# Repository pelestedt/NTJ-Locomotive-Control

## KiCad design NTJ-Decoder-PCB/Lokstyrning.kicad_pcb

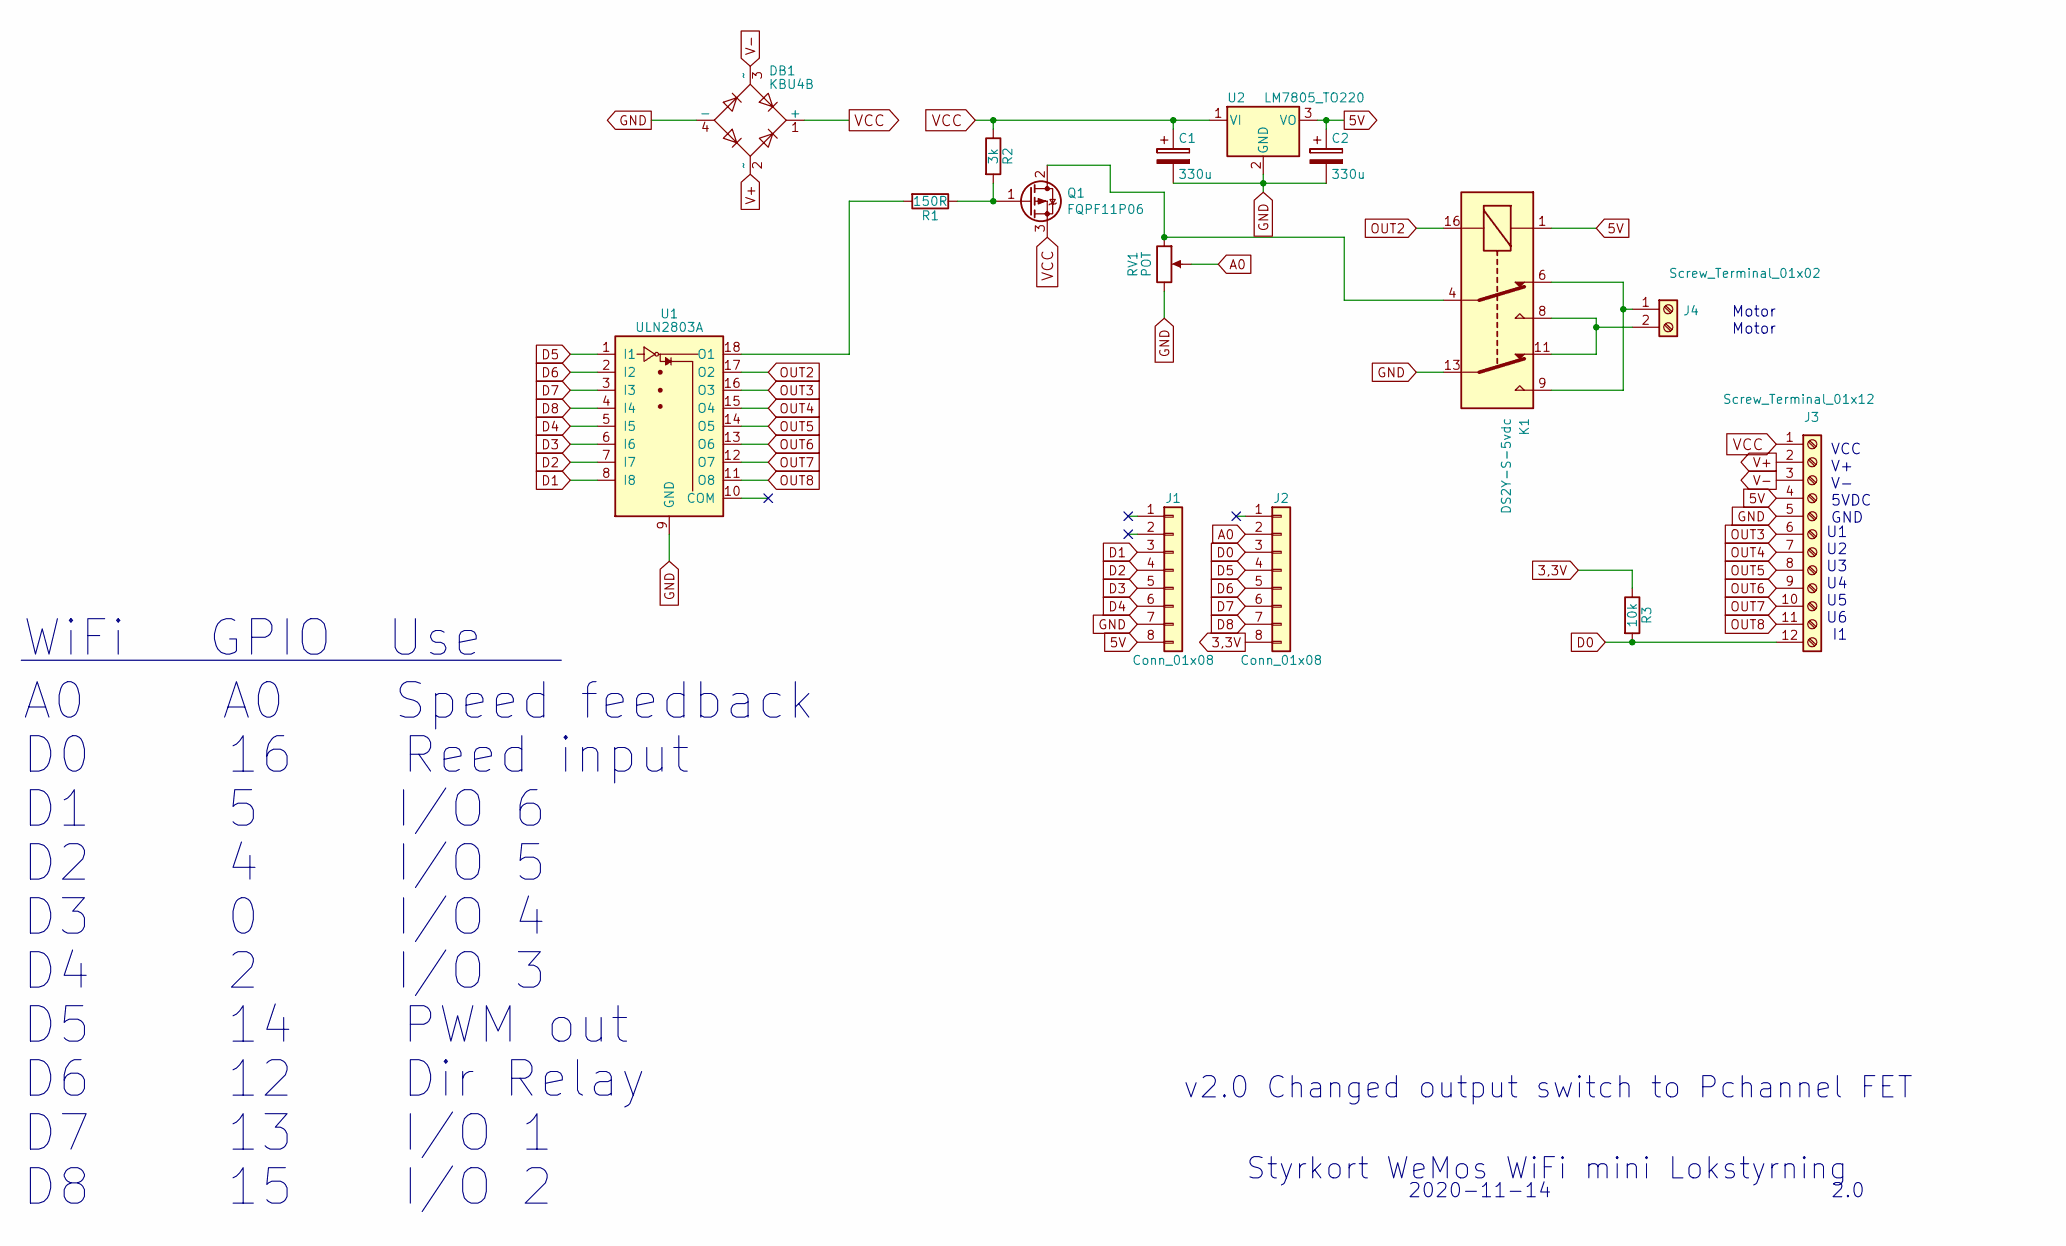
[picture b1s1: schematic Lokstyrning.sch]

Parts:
C1, C2: 330u; CP_Radial_D8.0mm_P5.00mm
DB1: KBU4B; Diode_Bridge_Vishay_KBU
J1, J2: Conn_01x08; Molex_SPOX-5267_22-03-5085_08x2.54mm_Straight
J3: Screw_Terminal_01x12; WAGO_734_12Pin_Straight_RuggedPads
J4: Screw_Terminal_01x02; WAGO_734_2pin_Straight_RuggedPads
K1: DS2Y-S-5vdc; Relay_SPST_OMRON-G5Q
Q1: FQPF11P06; TO-220_Vertical
R1: 150R; R_Axial_DIN0207_L6.3mm_D2.5mm_P10.16mm_Horizontal
R2: 3k; R_Axial_DIN0207_L6.3mm_D2.5mm_P10.16mm_Horizontal
R3: 10k; R_Axial_DIN0207_L6.3mm_D2.5mm_P10.16mm_Horizontal
RV1: POT; Potentiometer_Trimmer_ACP_CA14h5_Vertical_Px5.0mm_Py10.0mm
U1: ULN2803A; DIP-18_W7.62mm_LongPads
U2: LM7805_TO220; TO-220_Vertical

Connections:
3,3V: J2.8, R3.1
5V: C2.1, J1.8, J3.4, K1.1, U2.3 (VO)
A0: J2.2, RV1.2
D0: J2.3, J3.12, R3.2
D1: J1.3, U1.8 (I8)
D2: J1.4, U1.7 (I7)
D3: J1.5, U1.6 (I6)
D4: J1.6, U1.5 (I5)
D5: J2.4, U1.1 (I1)
D6: J2.5, U1.2 (I2)
D7: J2.6, U1.3 (I3)
D8: J2.7, U1.4 (I4)
GND: C1.2, C2.2, DB1.4 (-), J1.7, J3.5, K1.13, RV1.3, U1.9 (GND), U2.2 (GND)
unnamed: J4.1, K1.6, K1.9
unnamed: J4.2, K1.8, K1.11
unnamed: K1.4, Q1.2 (D), RV1.1
unnamed: Q1.1 (G), R1.1, R2.2
unnamed: R1.2, U1.18 (O1)
OUT2: K1.16, U1.17 (O2)
OUT3: J3.6, U1.16 (O3)
OUT4: J3.7, U1.15 (O4)
OUT5: J3.8, U1.14 (O5)
OUT6: J3.9, U1.13 (O6)
OUT7: J3.10, U1.12 (O7)
OUT8: J3.11, U1.11 (O8)
V+: DB1.2 (~~), J3.2
V-: DB1.3 (~~), J3.3
VCC: C1.1, DB1.1 (+), J3.1, Q1.3 (S), R2.1, U2.1 (VI)

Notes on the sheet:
D0 16 Reed input
D1 5 I/O 6
D2 4 I/O 5
A0 A0 Speed feedback
WiFi GPIO Use
D3 0 I/O 4
D4 2 I/O 3
D5 14 PWM out
D6 12 Dir Relay
D7 13 I/O 1
D8 15 I/O 2
Styrkort WeMos WiFi mini Lokstyrning
2020-11-14
2.0
U1 U2 U3 U4 U5 U6 I1
VCC V+ V- 5VDC GND
Motor Motor
v2.0 Changed output switch to Pchannel FET

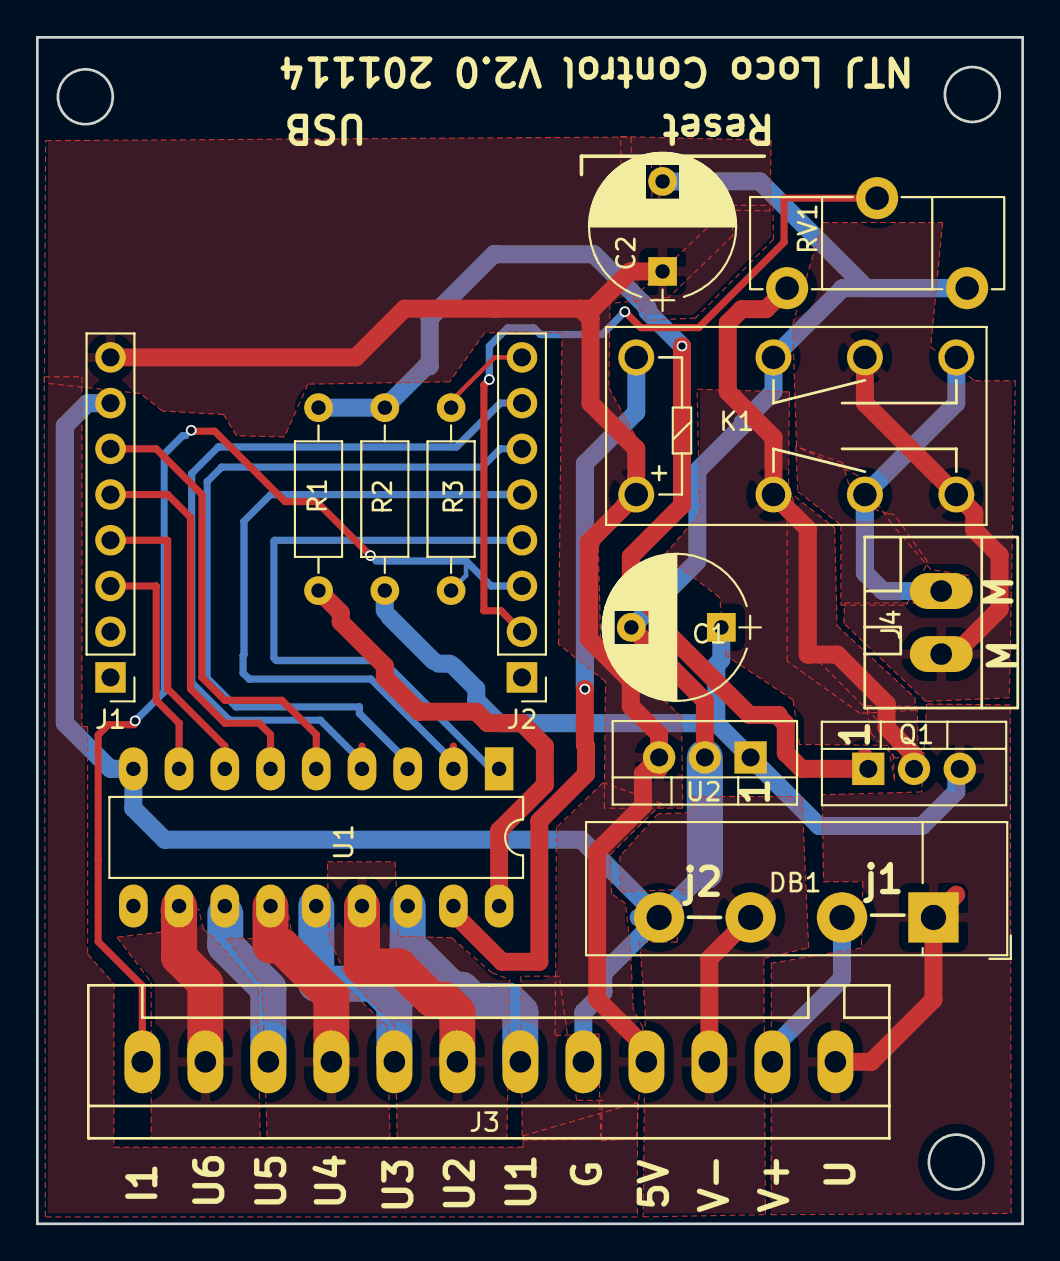
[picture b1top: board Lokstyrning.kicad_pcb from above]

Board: 2 copper layers, 54.7 x 65.9 mm, 15 parts (0 on the bottom side), 28 nets.

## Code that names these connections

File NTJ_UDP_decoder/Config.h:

/*
   Config.h

*/

/* Maximum WiFi clients that can be connected to WiThrottle */

String Configstring = "";         // a String to hold incoming data
boolean configmode = false;
int Inaddr;
String Configuration;
String Data;


//Main loop declarations
unsigned long last25run = 0;
unsigned long last50run = 0;
unsigned long last100run = 0;
unsigned long last400run = 0;
unsigned long last1000run = 0;
/* Define Control board I/O signals */
#define OUT1  D7 /*Define which GPIO corresponds to which output on the board*/
#define OUT2  D8
#define OUT3  D4
#define OUT4  D3
#define OUT5  D2
#define OUT6  D1
#define PWM  D5 /* Defines the GPIO for the PWM transistor control*/
#define DIR  D6 /* Defines the GPIO for the direction relay control*/
#define IN  D0 /* Defines the GPIO for the LED on the control board*/


long throttle_speed = 0; //0 to 126
int set_direction = 1; //1=forwrd 0=reverse
String namn;

long last=0;
long lastprint=0;

//getUDPdata declarations

String STASSID = "NTJ";
String STAPSK =  "NTJNTJ01";
int packetSize=0;

int myID = 999;
String Seq;

unsigned int localPort = 8888;      // local port to listen on
long lastparam1 = 0;
byte FunctionKey[30];

// buffer for sending data
char packetBuffer[20 + 1]; //buffer to hold incoming packet,

WiFiUDP Udp;

//Variabler lagrade i EEprom med defaultvärden angivna här
byte acceleration_time = 10; // FSet the time in seconds it should take for the locomotive to accelerate from standstill to full speed
byte deceleration_time = 10; //Set the time in seconds it should take for the locomotive to stop from full speed
int pwmfrq = 300;
int zero_speed = 10; //Set the PWM value where the locomotive, without load,starts to move
int fullspeed = 100;
int slowspeed = 75;
int halfspeed = 50;
int Shuntingspeed = 30;
int max_pulserate = 50;    //time between pulses in ms. If set to 0 the output will be only ON/OFF
int min_pulserate = 1000; //time between pulses in ms.If set to 0 the output will be only ON/OFF
int pulselength = 3;      //length of the sound generating puls relative the time between pulses in (1/(pulselength*actual pulselength))
int startwhistle = 20;
int approachwhistle = 30;
int smoke_timer = 0;
int creepspeed = 10;
int mindwell = 60;
int maxdwell = 240;
String ssid = "Ny_dekoder";
String loco_name = "Nytt_lok";
String password = "12345678";
int port = 44;
String hostn = "Ny_thserver";


//25ms declarations
boolean EMS = false;
boolean EMS_stopped = false;
float set_speed = 0;
float desired_speed = 0;
float current_PWM = 0;
float read_speed = 0;
float reglerfaktor = 40;
//int fixedpwm=50;

//50ms declarations
byte NSphase = 0;
byte NSRphase = 0;

//100ms declarations
byte NWphase = 0;
long nextwhistle = 0;


//400ms declarations
boolean NEXTSTATION = false;
boolean NEXTSTATIONREMOTE = false;
boolean PENDULUM = false;
boolean NEXTTIMER = false;
boolean sound = false;
boolean smoke = false;
boolean shunting = false;

//1000ms declarations
int smokeon = 0;

//Pendulum declarations
byte Pphase = 0;
long next = 0;
long startdwell = 0;
long dwelltime = 0;

/*PID working variables*/
unsigned long lastTime;
//double Input, Setpoint; Output, 
float ITerm, lastInput;
float kp, ki, kd;
int SampleTime = 25; //ms between samples
//double outMin, outMax;
//bool inAuto = false;
float error =0;
float dInput=0;

byte done=1;
long lastinc=0;
 
#define MANUAL 0
#define AUTOMATIC 1

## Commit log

2024-12-29 First version
2025-04-23 Uppladdning av aktuella filer
2025-07-26 Git fix
